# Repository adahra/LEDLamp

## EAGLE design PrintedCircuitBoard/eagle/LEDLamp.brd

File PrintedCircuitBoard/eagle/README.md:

EAGLE Directory

In this directory all electronic circuit board or PCB is stored.
The Software to create design of PCB is using [EAGLE](https://www.autodesk.com/products/eagle/overview).

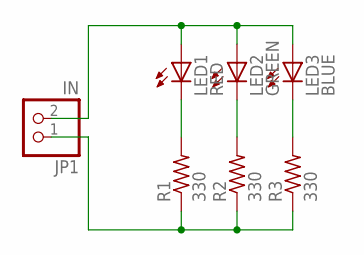
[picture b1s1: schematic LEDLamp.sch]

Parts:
JP1: IN; 1X02
LED1: RED; LED5MM
LED2: GREEN; LED5MM
LED3: BLUE; LED5MM
R1, R2, R3: 330; 0204/7

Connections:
unnamed: JP1.2, LED1.A, LED2.A, LED3.A
unnamed: LED1.K (C), R1.2
unnamed: LED2.K (C), R2.2
unnamed: LED3.K (C), R3.2
unnamed: JP1.1, R1.1, R2.1, R3.1

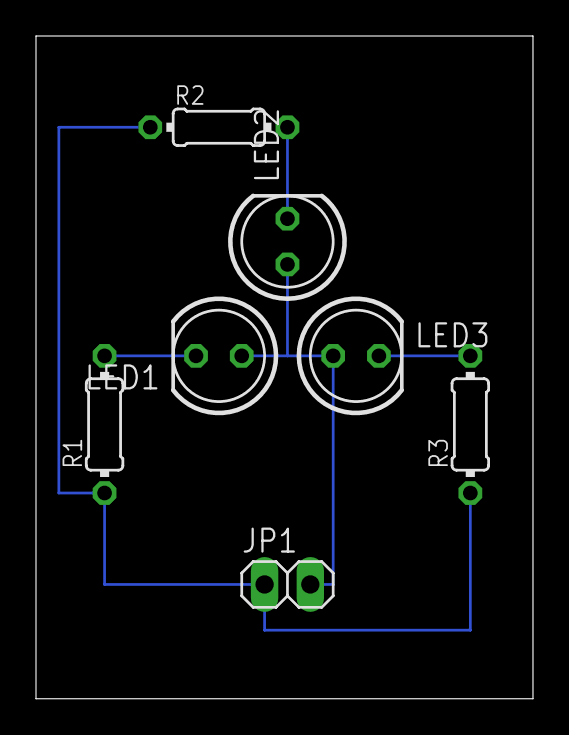
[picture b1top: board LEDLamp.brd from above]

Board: 2 copper layers, 27.6 x 36.8 mm, 8 parts (0 on the bottom side), 5 nets.

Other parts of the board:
DRILEGEND: DRILEGEND

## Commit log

2019-07-25 Added new readme file
2019-07-25 Added new description
2019-07-25 Added new description in readme
2019-08-15 Added new directory
2019-08-15 Added new readme on directory
2019-11-07 Added box case for store circuit board
2019-11-29 Added schematic of printed circuit board
